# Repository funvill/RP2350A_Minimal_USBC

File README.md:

# RP2350A Minimal Board KICad with USBC LCSC/JLCPCB parts

The primary goal of this project is to have a reference design for RP2350A, that uses USBC and has the LCSC/JLCPCB parts defined.

A secondary goal is to make the design physically small as possiable with one side SMD assembly.

**DO NOT USE** - This design has not been tested yet.

## Parts

- Microcontroller - [RP2350A](https://jlcpcb.com/partdetail/RaspberryPi-RP2350A/C42411118) (C42411118)
- Polarised inductor [Abracon AOTA-B201610S3R3-101-T](https://jlcpcb.com/partdetail/AbraconLlc-AOTA_B201610S3R3_101T/C42411119) (C42411119)
- Crystal oscillator [12 MHz Abracon ABM8-272-T3](https://jlcpcb.com/partdetail/AbraconLlc-ABM8_272T3/C20625731) (C20625731)
- 4Mb Flash - [Winbond Elec W25Q32JVUUIQ](https://jlcpcb.com/partdetail/WinbondElec-W25Q32JVUUIQ/C2999380) (C2999380)
- USB TYPE-C - [SHOU HAN USB TYPE-C 16PIN 2MD](https://jlcpcb.com/partdetail/ShouHan-TYPE_C_16PIN_2MD_073/C2765186) (C2765186) * Extended
- 3.3v Voltage Regulators - [AMS1117-3.3](https://jlcpcb.com/partdetail/Advanced_MonolithicSystems-AMS1117_33/C6186) (C6186)

## Design

The base design files came from [https://datasheets.raspberrypi.com/rp2350/Minimal-KiCAD.zip](https://datasheets.raspberrypi.com/rp2350/Minimal-KiCAD.zip)

I am trying to copy the power supply design from the [EasyEDA reference design with USBC](https://oshwlab.com/lckfb-team/coloreasypicox)

So that I can use the JLCPCB cupon here [RP2350 now available to buy: a high-performance, secure microcontroller for your next project](https://www.raspberrypi.com/news/rp2350-now-available-to-buy-a-high-performance-secure-microcontroller-for-your-next-project/)

## Helpful Links

- [KiCanvas](https://kicanvas.org/?github=https://github.com/funvill/RP2350A_Minimal_USBC/tree/main/RP-006440-DD-2-RP2350A%20Minimal%20Board%20Kicad%20archive) - In browser view of the KiCad files.
- [Hardware Design With RP2350](https://datasheets.raspberrypi.com/rp2350/hardware-design-with-rp2350.pdf)
- [EasyEDA2Kicad](https://github.com/uPesy/easyeda2kicad.py) - Converts JLCPCB parts to KiCad files.

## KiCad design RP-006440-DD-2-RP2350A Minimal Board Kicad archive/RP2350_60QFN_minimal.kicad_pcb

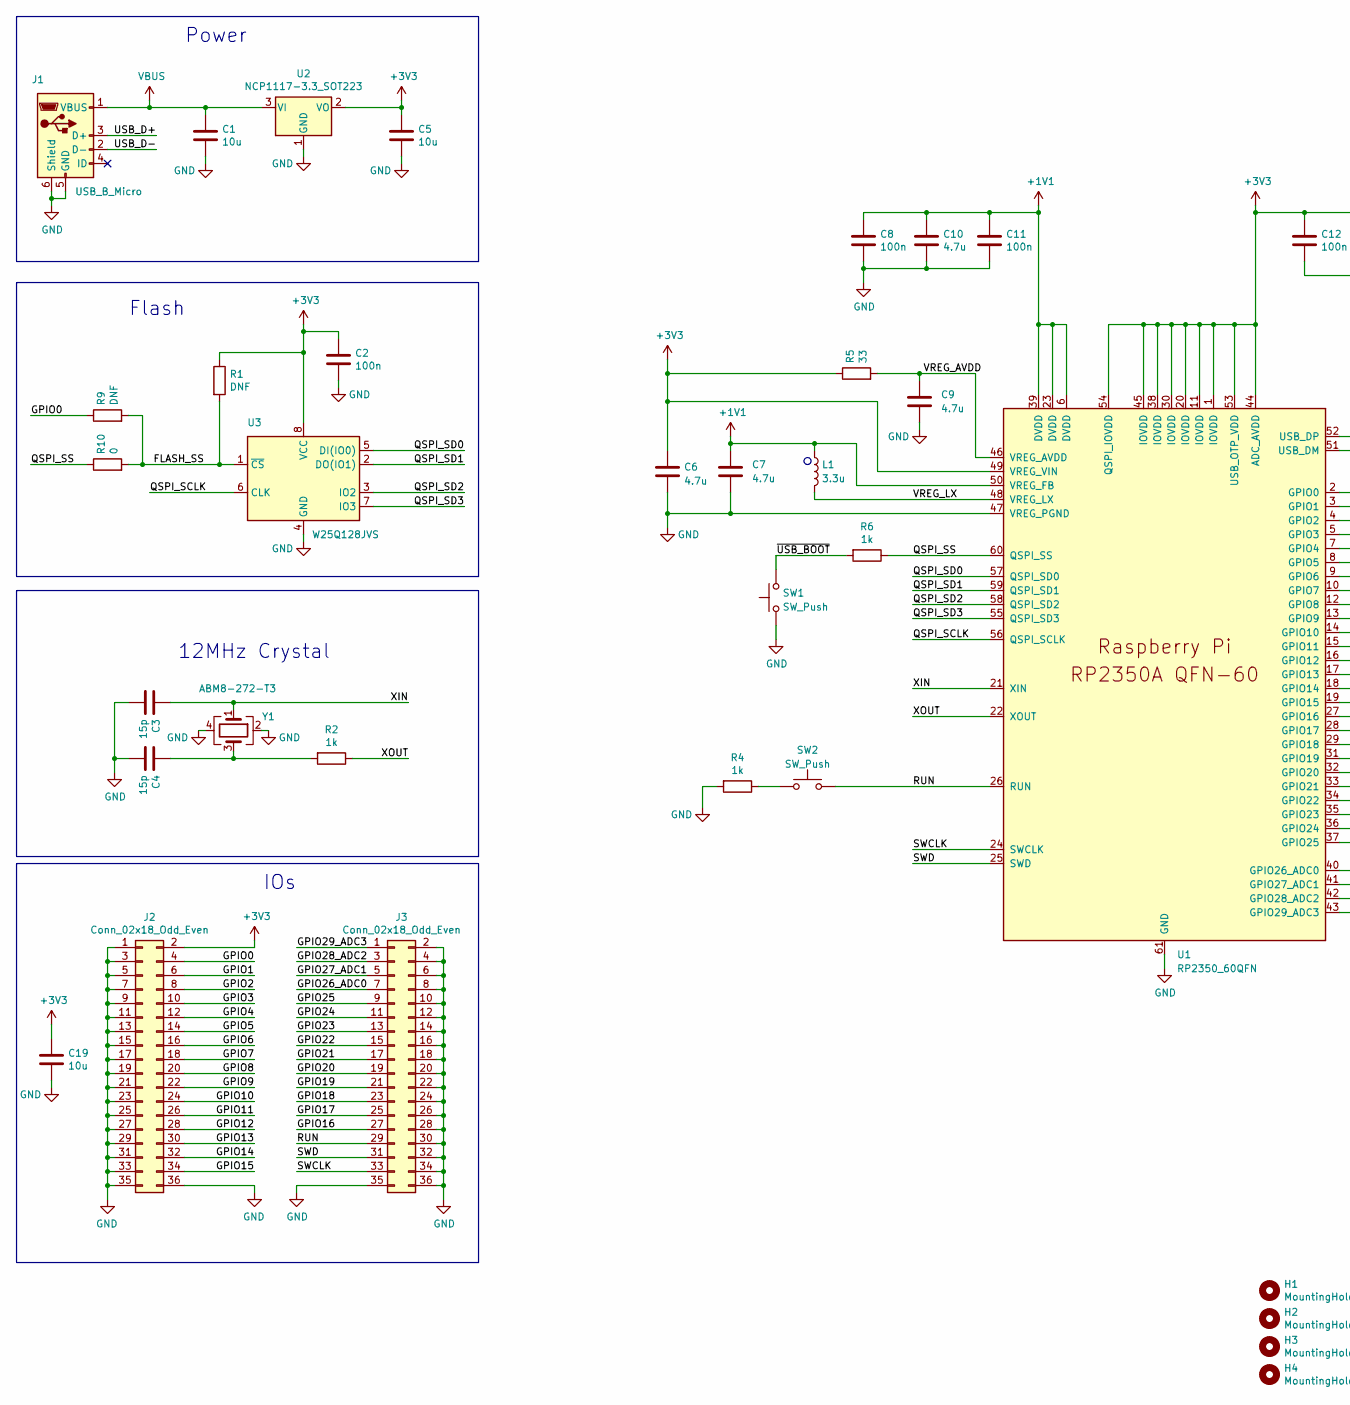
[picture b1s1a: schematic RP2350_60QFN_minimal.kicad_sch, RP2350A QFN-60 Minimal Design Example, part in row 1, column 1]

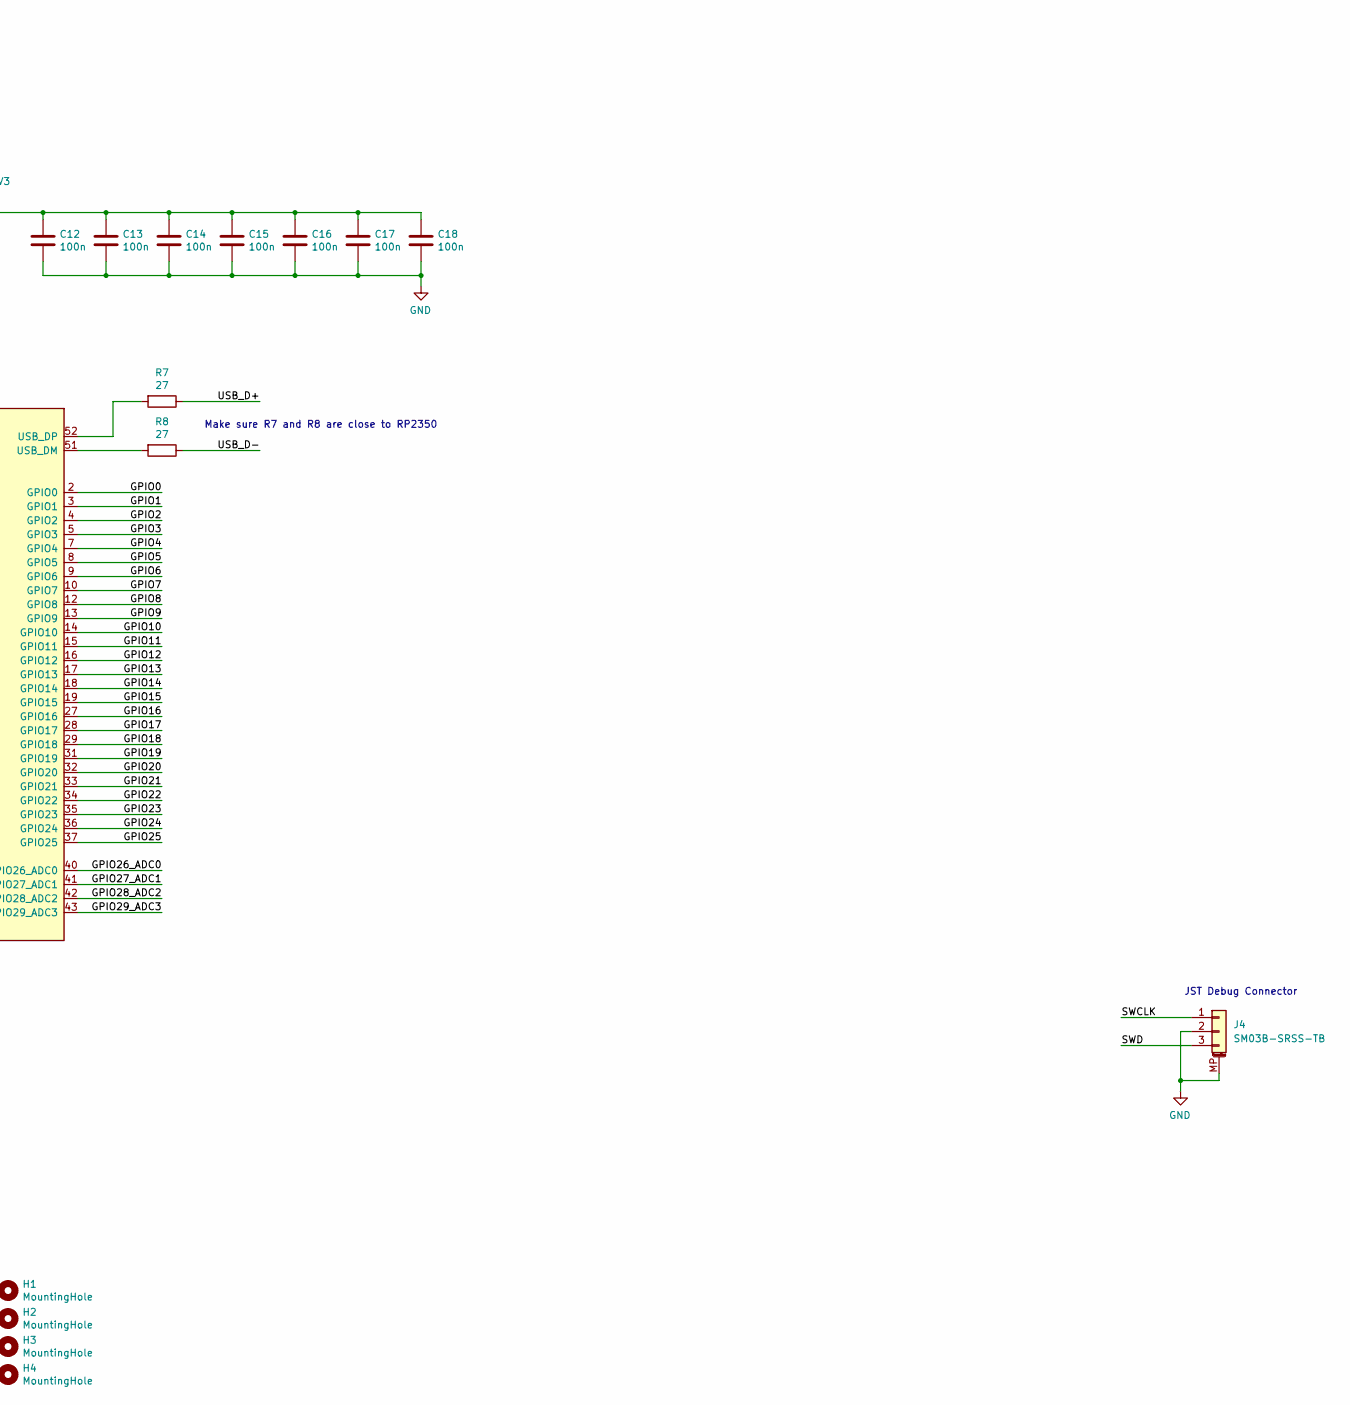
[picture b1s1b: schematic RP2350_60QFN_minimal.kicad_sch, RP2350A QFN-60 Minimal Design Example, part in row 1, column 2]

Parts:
C1, C5, C19: 10u; C_0805_2012Metric
C2, C8, C11, C12, C13, C14, C15, C16, C17, C18: 100n; C_0402_1005Metric
C3, C4: 15p; C_0402_1005Metric
C6, C7: 4.7u; C_0402_1005Metric_small_pads
C9, C10: 4.7u; C_0402_1005Metric
H1, H2, H3, H4: MountingHole; MountingHole_2.7mm_M2.5
J1: USB_B_Micro; USB_Micro-B_Amphenol_10103594-0001LF_Horizontal
J2, J3: Conn_02x18_Odd_Even; PinHeader_2x18_P2.54mm_Vertical
J4: SM03B-SRSS-TB; JST_SH_SM03B-SRSS-TB_1x03-1MP_P1.00mm_Horizontal
L1: 3.3u; L_pol_2016; LCSC Part C42411119
R1, R9: DNF; R_0402_1005Metric
R2, R4, R6: 1k; R_0402_1005Metric
R5: 33; R_0402_1005Metric
R7, R8: 27; R_0402_1005Metric
R10: 0; R_0402_1005Metric
SW1, SW2: SW_Push; SW_Push_1P1T_NO_Vertical_Wuerth_434133025816
U1: RP2350_60QFN; RP2350-QFN-60-1EP_7x7_P0.4mm_EP3.4x3.4mm_ThermalVias; LCSC Part C42411118
U2: NCP1117-3.3_SOT223; SOT-223-3_TabPin2
U3: W25Q128JVS; SOIC-8_5.23x5.23mm_P1.27mm; LCSC Part C2999380
Y1: ABM8-272-T3; Crystal_SMD_3225-4Pin_3.2x2.5mm; LCSC Part C20625731

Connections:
+1V1: C7.1, C8.1, C10.1, C11.1, L1.1, U1.6 (DVDD), U1.23 (DVDD), U1.39 (DVDD), U1.50 (VREG_FB)
+3V3: C2.1, C5.1, C6.1, C12.1, C13.1, C14.1, C15.1, C16.1, C17.1, C18.1, C19.1, J2.2, R1.1, R5.1, U1.1 (IOVDD), U1.11 (IOVDD), U1.20 (IOVDD), U1.30 (IOVDD), U1.38 (IOVDD), U1.44 (ADC_AVDD), U1.45 (IOVDD), U1.49 (VREG_VIN), U1.53 (USB_OTP_VDD), U1.54 (QSPI_IOVDD), U2.2 (VO), U3.8 (VCC)
/FLASH_SS: R1.2, R9.2, R10.2, U3.1 (~CS)
/GPIO0: J2.4, R9.1, U1.2 (GPIO0)
/GPIO1: J2.6, U1.3 (GPIO1)
/GPIO2: J2.8, U1.4 (GPIO2)
/GPIO3: J2.10, U1.5 (GPIO3)
/GPIO4: J2.12, U1.7 (GPIO4)
/GPIO5: J2.14, U1.8 (GPIO5)
/GPIO6: J2.16, U1.9 (GPIO6)
/GPIO7: J2.18, U1.10 (GPIO7)
/GPIO8: J2.20, U1.12 (GPIO8)
/GPIO9: J2.22, U1.13 (GPIO9)
/GPIO10: J2.24, U1.14 (GPIO10)
/GPIO11: J2.26, U1.15 (GPIO11)
/GPIO12: J2.28, U1.16 (GPIO12)
/GPIO13: J2.30, U1.17 (GPIO13)
/GPIO14: J2.32, U1.18 (GPIO14)
/GPIO15: J2.34, U1.19 (GPIO15)
/GPIO16: J3.27, U1.27 (GPIO16)
/GPIO17: J3.25, U1.28 (GPIO17)
/GPIO18: J3.23, U1.29 (GPIO18)
/GPIO19: J3.21, U1.31 (GPIO19)
/GPIO20: J3.19, U1.32 (GPIO20)
/GPIO21: J3.17, U1.33 (GPIO21)
/GPIO22: J3.15, U1.34 (GPIO22)
/GPIO23: J3.13, U1.35 (GPIO23)
/GPIO24: J3.11, U1.36 (GPIO24)
/GPIO25: J3.9, U1.37 (GPIO25)
/GPIO26_ADC0: J3.7, U1.40 (GPIO26_ADC0)
/GPIO27_ADC1: J3.5, U1.41 (GPIO27_ADC1)
/GPIO28_ADC2: J3.3, U1.42 (GPIO28_ADC2)
/GPIO29_ADC3: J3.1, U1.43 (GPIO29_ADC3)
/QSPI_SCLK: U1.56 (QSPI_SCLK), U3.6 (CLK)
/QSPI_SD0: U1.57 (QSPI_SD0), U3.5 (DI(IO0))
/QSPI_SD1: U1.59 (QSPI_SD1), U3.2 (DO(IO1))
/QSPI_SD2: U1.58 (QSPI_SD2), U3.3 (IO2)
/QSPI_SD3: U1.55 (QSPI_SD3), U3.7 (IO3)
/QSPI_SS: R6.1, R10.1, U1.60 (QSPI_SS)
/RUN: J3.29, SW2.2, U1.26 (RUN)
/SWCLK: J3.33, J4.1, U1.24 (SWCLK)
/SWD: J3.31, J4.3, U1.25 (SWD)
/USB_D+: J1.3 (D+), R7.1
/USB_D-: J1.2 (D-), R8.1
/VREG_AVDD: C9.1, R5.2, U1.46 (VREG_AVDD)
/VREG_LX: L1.2, U1.48 (VREG_LX)
/XIN: C3.1, U1.21 (XIN), Y1.1
/XOUT: R2.1, U1.22 (XOUT)
/~USB_BOOT: R6.2, SW1.2
GND: C1.2, C2.2, C3.2, C4.2, C5.2, C6.2, C7.2, C8.2, C9.2, C10.2, C11.2, C12.2, C13.2, C14.2, C15.2, C16.2, C17.2, C18.2, C19.2, J1.5 (GND), J1.6 (Shield), J2.1, J2.3, J2.5, J2.7, J2.9, J2.11, J2.13, J2.15, J2.17, J2.19, J2.21, J2.23, J2.25, J2.27, J2.29, J2.31, J2.33, J2.35, J2.36, J3.2, J3.4, J3.6, J3.8, J3.10, J3.12, J3.14, J3.16, J3.18, J3.20, J3.22, J3.24, J3.26, J3.28, J3.30, J3.32, J3.34, J3.35, J3.36, J4.2, J4.MP (MountPin), R4.2, SW1.1, U1.47 (VREG_PGND), U1.61 (GND), U2.1 (GND), U3.4 (GND), Y1.2, Y1.4
unnamed: C4.1, R2.2, Y1.3
unnamed: R4.1, SW2.1
unnamed: R8.2, U1.51 (USB_DM)
unnamed: R7.2, U1.52 (USB_DP)
VBUS: C1.1, J1.1 (VBUS), U2.3 (VI)

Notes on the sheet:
JST Debug Connector
IOs
Flash
Make sure R7 and R8 are close to RP2350
12MHz Crystal
Power

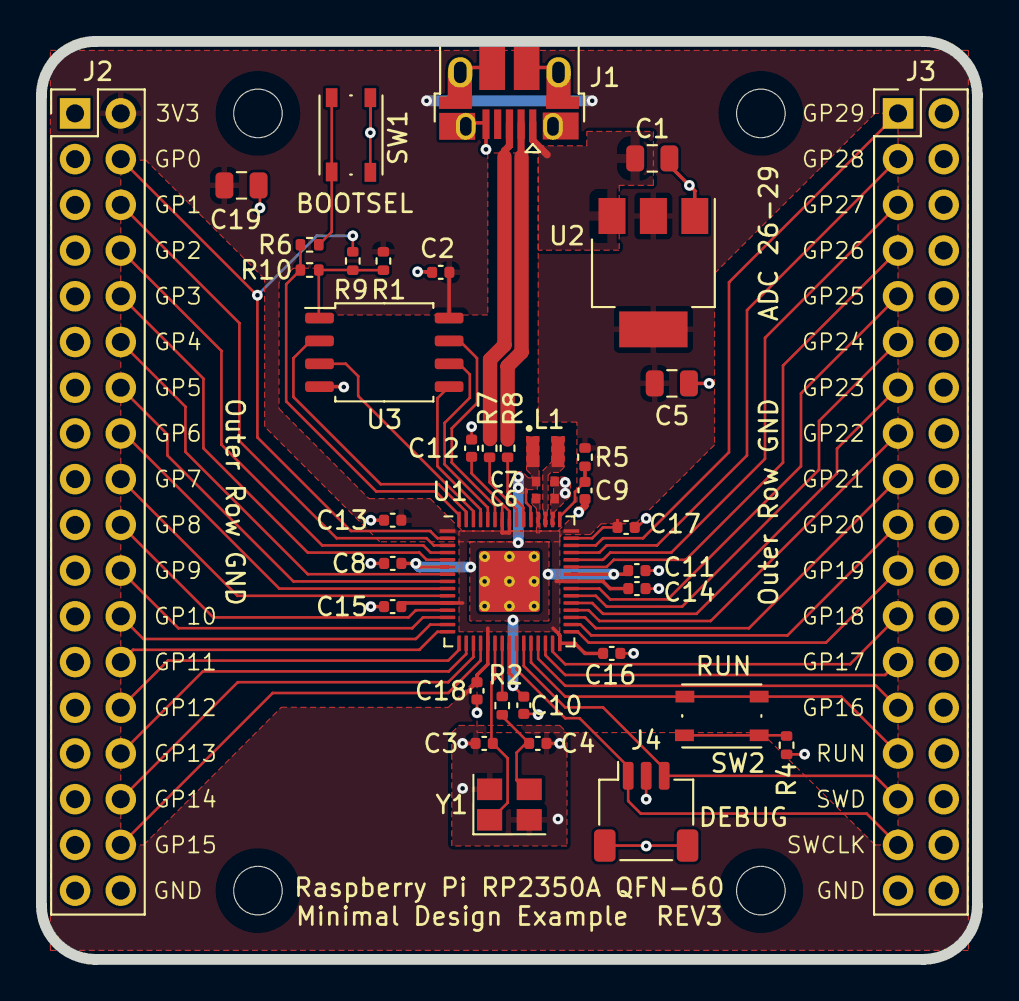
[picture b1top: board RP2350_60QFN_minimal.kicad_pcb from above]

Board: 2 copper layers, 52.0 x 51.0 mm, 43 parts (0 on the bottom side), 55 nets.

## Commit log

2025-03-18 Updated readme and some of the JLCPCB parts
2025-03-18 Updated the KiCanvas link
2025-03-19 Updated with USB-C circuit for review
